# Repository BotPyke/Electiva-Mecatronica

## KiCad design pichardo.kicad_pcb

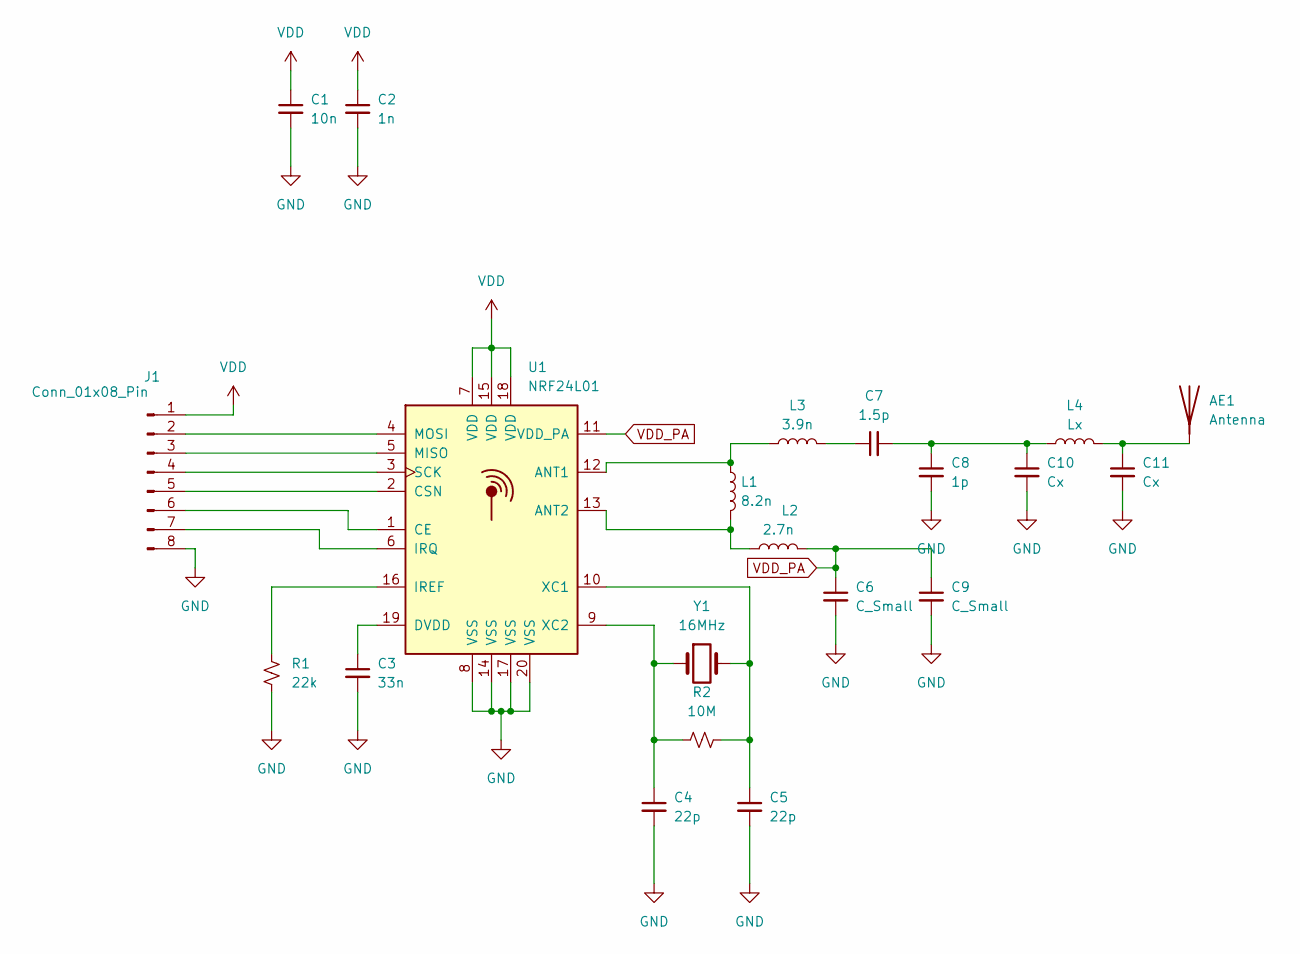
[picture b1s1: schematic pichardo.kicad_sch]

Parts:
AE1: Antenna; Texas_SWRA117D_2.4GHz_Right
C1: 10n; C_0402_1005Metric
C2: 1n; C_0402_1005Metric
C3: 33n; C_0402_1005Metric
C4, C5: 22p; C_0402_1005Metric
C6, C9: C_Small; C_0402_1005Metric
C7: 1.5p; C_0402_1005Metric
C8: 1p; C_0402_1005Metric
C10, C11: Cx; C_0402_1005Metric
J1: Conn_01x08_Pin; Hirose_DF13-08P-1.25DSA_1x08_P1.25mm_Vertical
L1: 8.2n; L_0402_1005Metric
L2: 2.7n; L_0402_1005Metric
L3: 3.9n; L_0402_1005Metric
L4: Lx; L_0402_1005Metric
R1: 22k; R_0402_1005Metric
R2: 10M; R_0402_1005Metric
U1: NRF24L01; QFN-20-1EP_4x4mm_P0.5mm_EP2.5x2.5mm
Y1: 16MHz; Crystal_SMD_3215-2Pin_3.2x1.5mm

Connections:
GND: C1.2, C2.2, C3.2, C4.2, C5.2, C6.2, C8.2, C9.2, C10.2, C11.2, J1.8, R1.2, U1.8 (VSS), U1.14 (VSS), U1.17 (VSS), U1.20 (VSS)
unnamed: AE1.1 (A), C11.1, L4.2
unnamed: C7.1, L3.2
unnamed: C7.2, C8.1, C10.1, L4.1
unnamed: J1.2, U1.4 (MOSI)
unnamed: J1.3, U1.5 (MISO)
unnamed: J1.4, U1.3 (SCK)
unnamed: J1.5, U1.2 (CSN)
unnamed: J1.6, U1.1 (CE)
unnamed: J1.7, U1.6 (IRQ)
unnamed: L1.1, L3.1, U1.12 (ANT1)
unnamed: L1.2, L2.1, U1.13 (ANT2)
unnamed: C3.1, U1.19 (DVDD)
unnamed: R1.1, U1.16 (IREF)
unnamed: C5.1, R2.2, U1.10 (XC1), Y1.2
unnamed: C4.1, R2.1, U1.9 (XC2), Y1.1
VDD: C1.1, C2.1, J1.1, U1.7 (VDD), U1.15 (VDD), U1.18 (VDD)
VDD_PA: C6.1, C9.1, L2.2, U1.11 (VDD_PA)

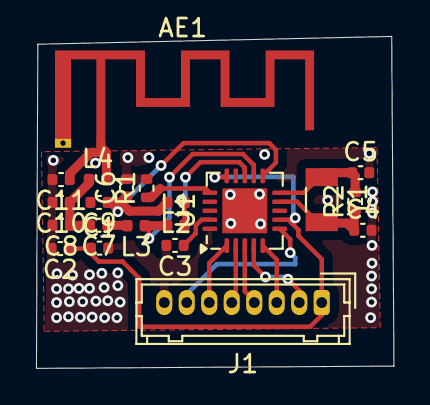
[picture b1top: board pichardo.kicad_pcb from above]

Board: 2 copper layers, 19.9 x 18.4 mm, 21 parts (0 on the bottom side), 18 nets.

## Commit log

2024-10-05 Resumen
2024-12-06 Create Esp32
2024-12-06 Creacion de Pcb de Video
2024-12-06 Resumen2
2024-12-07 Plantilla de Especificacion
